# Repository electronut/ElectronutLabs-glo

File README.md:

# glo

glo is a tiny programmable RGB LED based on ATtiny13. The idea is that it can
be a "smart" drop-in replacement for a regular LED. For example, the LED could
flash in a pre-programmed way, or respond to analog input on the GPIO pin.

Specifications:

- Atmel ATtiny13 (10M1 package)
- Common cathode RGB LED
- 3 Pins - VCC, GND, GPIO
- Standard 2x3 ICSP header (pads) for programming
- Can be programmed using a Pogo Pin programmer or equivalent

glo on hackaday:

https://hackaday.io/project/18083-glo

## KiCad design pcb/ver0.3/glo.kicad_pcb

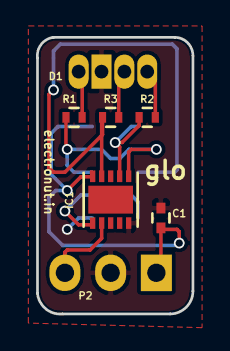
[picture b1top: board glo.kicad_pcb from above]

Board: 2 copper layers, 8.6 x 15.4 mm, 8 parts (1 on the bottom side), 10 nets.

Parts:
C1: 0.1uF; C_0402
D1: LED_RCBG; LED-RGB-5MM_Common_Cathode
IC1: ATTINY13-MM; attiny13a
P1: ICSP; pogo_prog_2x3
P2: PWR; Pin_Header_Angled_1x03
R1: 200; R_0402
R2, R3: 100; R_0402

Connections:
GND: C1.2, D1.2, IC1.5, P1.6, P2.2
MISO: IC1.7, P1.1, R2.1
MOSI: IC1.6, P1.4, R1.1
unnamed: D1.1, R1.2
unnamed: D1.3, R3.2
unnamed: D1.4, R2.2
unnamed: IC1.2, P2.3
RESET: IC1.1, P1.5
SCK: IC1.9, P1.3, R3.1
VCC: C1.1, IC1.10, P1.2, P2.1

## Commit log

2016-11-10 updated with code etc
